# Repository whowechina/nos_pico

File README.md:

# Nos Pico - Nostalgia Style Mini Controller
[点这里可以切换到中文版](README_CN.md)

Currently there're two sizes of Nos Pico. Nos Pico is the small one, suitable for 15 to 17 inch monitors. Nos Pico+ is the larger one, suitable for 24 to 27 inch monitors. There're no differences except the size.

Features:
* All 3D printed parts.
* Velocity sensitive.
* RGB key lights.
* Works as MIDI keyboard.
* HID lights.
* 4 extra programmable buttons.

Thanks to many respectful guys/companies who made their tools or materials free or open source (KiCad, OnShape, InkScape, Raspberry things).

Special thanks to community projects and developers.
And also these projects:
* RP_Silicon_KiCad: https://github.com/HeadBoffin/RP_Silicon_KiCad
* Type-C: https://github.com/ai03-2725/Type-C.pretty

## My Other Projects
You can check out my other cool projects.

* Popn Pico: https://github.com/whowechina/popn_pico
* IIDX Pico: https://github.com/whowechina/iidx_pico
* Chu Pico: https://github.com/whowechina/chu_pico
* Mai Pico: https://github.com/whowechina/mai_pico
* Diva Pico: https://github.com/whowechina/diva_pico
* AIC Pico: https://github.com/whowechina/aic_pico
* Groove Pico: https://github.com/whowechina/groove_pico
* Geki Pico: https://github.com/whowechina/geki_pico
* Musec Pico: https://github.com/whowechina/musec_pico
* Ju Pico: https://github.com/whowechina/ju_pico
* Bishi Pico: https://github.com/whowechina/bishi_pico
* Nos Pico: https://github.com/whowechina/nos_pico
* Voltex Pico: https://github.com/whowechina/voltex_pico
* Chord Pico: https://github.com/whowechina/chord_pico
* Dance Pico: https://github.com/whowechina/dance_pico
* Arcade Pico: https://github.com/whowechina/arcade_pico

## **Disclaimer** ##
I made this project in my personal time with no financial benefit or sponsorship. I will continue to improve the project. I have done my best to ensure that everything is accurate and functional, there's always a chance that mistakes may occur. I cannot be held responsible for any loss of your time or money that may result from using this open source project. Thank you for your understanding.

## About the License
It's CC-NC. So DIY for yourself and for your friend, don't make money from it. And plagiarism that doesn’t even dare to mention the original author is not acceptable. Please note that pooling orders and group buying for raw materials is acceptable.Selling any leftover components at cost (without profit) is also acceptable.

If you're interested in buying from me, or for commercial use, please contact me (Discord, QQ group, Goofish).
* My Discord Invitation: https://discord.gg/M8f2PPQFEA
* QQ Group: 854535476
* Goofish: whowe12345

## HOW TO BUILD
### PCB and Components
* Go JLCPCB or any PCB vendor you like, make order with the gerber zip files (latest `Production\PCB\nos_pico_xxx.zip` for Nos Pico, or `Production\PCB\nos_plus_xxx.zip` for Nos Pico+), regular FR-4 board, black color, **1.6mm** thickness.

* 1x Rasberry Pico Pi Pico or pin-to-pin compatible clones, those with type-C port are strongly recommended.  
  https://www.raspberrypi.com/products/raspberry-pi-pico
* 1x USB Type-C socket (918-418K2023S40001 or KH-TYPE-C-16P)

* 1x ADG732BSUZ (TQFP48) analog multiplexer.  
  https://www.analog.com/en/products/adg732.html
* 1x MBR120VLSFT1G Schottky diode (SOD-123), or any SOD-123 **Schottky** diode with 1A or more current rating.
* 20x to 30x 0603 0.1uF (0.1~1uF all fine) capacitors.
* 3x 0603 5.1kohm resistors, 2 for USB and 1 for signal divider.
* 1x 0603 2kohm resistor for signal divider.
* 28x SS49E linear Hall effect sensors (SOT23).
* 1x Small 3V to 5V DC-DC step up or up-down converter. Make sure its output is 5V and input range covers 3.3V. If the one you get has different pinout, you need to hand wire it. If you don't see the footprint in the PCB, that means it's removed from newer revisions.  
  https://www.dfrobot.com/product-1766.html

* for Nos Pico only:
  * 56x WS2812B-4020 RGB LEDs (side facing)
  * 6x WS2812B-3528 RGB LEDs.
  * 4x HDK KSMC614A or Alps SKRGASD010 switches (6mm\*6mm\*9.5mm).  
    https://www.hdk.co.jp/pdf/spj/spj_ksmc614a.pdf  
    https://www.mouser.com/datasheet/2/15/alps_s_a0002902192_1-2258679.pdf
    
* for Nos Pico+ only:
  * 62x WS2812B-3528 RGB LEDs.
  * 4x Kailh Box Cream Pro switches.  
    https://www.kailh.net/products/kailh-box-cream-pro-switch-set

* Note: in newer revisions, the DC/DC is removed, use the following components instead.
  * 1x TPS7A2042PDBVR (4.2V) or LP5907MFX-4.5 (4.5V) LDO (SOT23-5), (U7).  
    https://www.ti.com/product/TPS7A20/part-details/TPS7A2042PDBVR
  * 1x LM4040 3.0V Shunt Voltage Reference, in SOT23-3 (U6). There're many models; make sure it's 3.0V and in an SOT23-3 package.
  * R1 and R2 are 2Kohm and 5.1Kohm 0603 resistors, respectively.

* This is how Nos Pico looks after soldering.  

* This is how Nos Pico+ looks after soldering.  

### Notes
1. About the 2 USB holes, you decide whether to solder them or not.   

   * If you solder these 2 hole pins.
     * Pros: ether USB ports can be used for host communication; if your pico has a micro USB port, now you'll have a Type-C port and a micro USB port.
     * Cons: if one port is for host communication, the other port can use for power supply, but only from power bank or charger, not from a USB data port.

   * Or you don't solder them (and also better use thin tape to cover the pins on Pi Pico).
     * Pros: only the port from Pi Pico can be used for host communication, the other port can only be used for power supply.
     * Cons: the power supply port can connect to any USB port, inluding USB data ports, power banks or chargers.

2. There're so many capacitors for de-coupling. You don't need to solder them all. You can solder some of them, just distribute them evenly. The one near the multiplexer is a must.

3. Leave C30 un-soldered.

### Test the PCB
* You can test the PCB now, put the firmware in.
* Very likely all key LEDs will light up in white.
* Logo LEDs will slowly change color.
* Nos Pico should be recognized as a USB HID device, here's the test page.  
  https://greggman.github.io/html5-gamepad-test/
* The test page responds to the 4 button switches.
* Use the terminal tool to connect to Nos Pico's command line interface.
  https://googlechromelabs.github.io/serial-terminal/
* Keep the PCB away from magnetic field, such as speakers or motors and execute `calibrate origin`. All values should be similar and near 2200.
* If you notice strange values, you need to check the soldering of the muxiplexer and corresponding hall effect sensor.

### 3D Printing
#### Printing parameters  
* PLA or PETG.
* Layer height: 0.2mm
* Wall: 2 to 3.
* Support: No, unless explicitly mentioned.
* Files are always in milimeter unit, not inch.

#### Parts
* All files are in `Production\3DPrint` folder.
* File names started with `Nos Pico -` are for Nos Pico, and `Nos Pico+ -` are for Nos Pico+.

* Keys: `Key.3mf`. Print 28 keys, 8 all-white, and 20 white-with-black tops (with "black key"). You need multi-color printing for the keys, or you need to manually paint the black part.  
  
* Base: `Base_*.stl`, all in light apricot color.
* Rear: `Rear_*.stl`, all in light apricot color. Make the side with the screws as the bottom and **enable support**.
* Support: `Support_*.stl`, Left and Right are in light apricot color and Center is in white color.
* Panel: `Panel_*.stl`, Left and Right are in light apricot color. The Center is in white color with the black logo on top. You can use multi-color to print it or paint it manually.

### Assembly
#### Other components needed
Please note that the quantities of the screws are approximate.

* 10x M3\*6mm screws for the PCB to the base parts.
* 20x M3\*8mm screws for support parts to the base parts.
* 16x M3\*8mm screws for rear parts to the base parts.
* 20x M2\*8mm countersunk screws for the panels to the support parts.
* Some 2.5mm~3mm thick self-adhesive foam tape (Poron or EVA).
* Some 1mm~1.5mm thick self-adhesive foam tape (Poron or EVA).

* 28x 0.4\*5\*10\*6N (0.4mm wire diameter, 5mm outer diameter, 10mm free length, 6 turns) springs.
* Some white silicone adhesive, such as K-704 silicone industrial adhesive.

* Some 10mm diameter silicone self-adhesive anti-slip pads.  

* For Nos Pico only.
  * 1x 2mm\*361mm stainless steel wire shaft.
  * 28x 2mm\*2mm axial magnetized cylinder magnets (2mm diameter, 2mm height).

* For Nos Pico+ only.
  * 1x 2mm\*573mm stainless steel wire shaft.
  * 28x 3mm\*2mm axial magnetized cylinder magnets (3mm diameter, 2mm height).

#### Steps
Please note that the pictures in this section are mixed with Nos Pico and Nos Pico+, some are even from prototype. But the assembly steps are the same. So ignore the differences in some details.

1. Use the M3\*6mm screws to fix the PCB to the base part.  
   
2. Apply the 2.5mm thick foam tape on PCB, right below the hall effect sensors. It damps the key press noise. 3mm width is recommended for Nos Pico, and 5mm width is recommended for Nos Pico+.  
   
3. Use the M3*8mm screws to fix the support parts to the base part.  
   
4. Insert the steel shafts into keys and install them into the base parts. Please note the key arrangements.  

5. Rotate the keys to the other side to insert the magnets into the keys. Cylinder magnets should be placed vertically. You need some glue or silicone adhesive to fix them in place.

6. Install the springs on the base parts, and rotate the keys onto them.

7. Now we temporarily calibrate and test the keys use `calibrate travel` command. Leave the keys un-pressed before executing the command, 1 second later, gently press down all the keys (not neccessarily all of them simultanously, just to cover them all). After calibration, keys are ready for play. You can use some MIDI software to test the keys. If all keys work fine, you can proceed to the next step. If not, you need to check the soldering of the hall effect sensors and the multiplexer.  
   
8. Apply the 1mm thick foam tape on the edge of the panel parts. It damps the key release noise.  
   
9.  Use the M2*8mm countersunk screws to fix the panel parts to the support parts.  
    
10. Use the M3*10mm screws to fix the rear parts to the base parts. Please note that left and right rear parts have a shaft limit slot, which is blocked by thin walls working as print support, you need to cut them open.  
    
11. Now calibrate the key travel again use `calibrate travel` command, don't forget to gently press down all the keys 1 second after executing the command.
12. Apply the silicone self-adhesive anti-slip pads on the bottom of the base parts.  
    
13. Congratulations, you finished!

#### Caution
* Don't use `calibrate origin` command after the assembly. It can only be used when there's no magnets installed.
* Screws are easy to break 3D printed parts. So don't screw them too fast or too tight. When you notice the resistance suddenly increases, stop immediately.

### Firmware
* UF2 file is in `Production\Firmware` folder.
* For the new build, hold the BOOTSEL button while connect the USB to a PC, there will be a disk named "RPI-RP2" showed up. Drag the UF2 firmware binary file into it. That's it. Note that there's a small hole on the bottom side of the Nos Pico, aligned with the BOOTSEL button.
* If it's already running Nos Pico firmware, you can either use "update" in command line or hold down left 2 buttons while connecting to USB to enter update mode.
* To access the command line, you can use this Web Serial Terminal to connect to the command line port of the controller. (Note: "?" is for help)  
  https://googlechromelabs.github.io/serial-terminal/

### Usage
* By default, it works as a MIDI keyboard. Just plug and play.
* You can change the report to HID buttons, or HID analog values (axis) with `hid *` command.
* You can change the key light mode using `light *` command.
* You can change the light brightness using `level <key|logo>` command.
* You can do live setting without the command line interface. Let's call the 4 auxilary keys are L1, L2, R1, R2. Pressing all of them at the same time will enter the live setting mode.
  * L1 and L2 are for navigating the setting items. The logo light shows current item. The items are:
    * Brightness for Piano Key Light
    * Brightness for Logo Light
    * Piano Key Light Mode (Off, Switch, Pressure, Velocity)
  * R1 is Cancel, R2 is Confirm.
  * The piano keys are for changing the values of the setting items.  

## CAD Source File
I'm using OnShape free subscription. It's powerful but it can't archive original designs to local, so I can only share the link here. STL/DXF/DWG files are exported from this online document.  
  https://cad.onshape.com/documents/0429d4b0d9d82f8289fdce7e/w/647e985c461e79dd4ff63d99/e/9dea2fe40b32c7a64632a585

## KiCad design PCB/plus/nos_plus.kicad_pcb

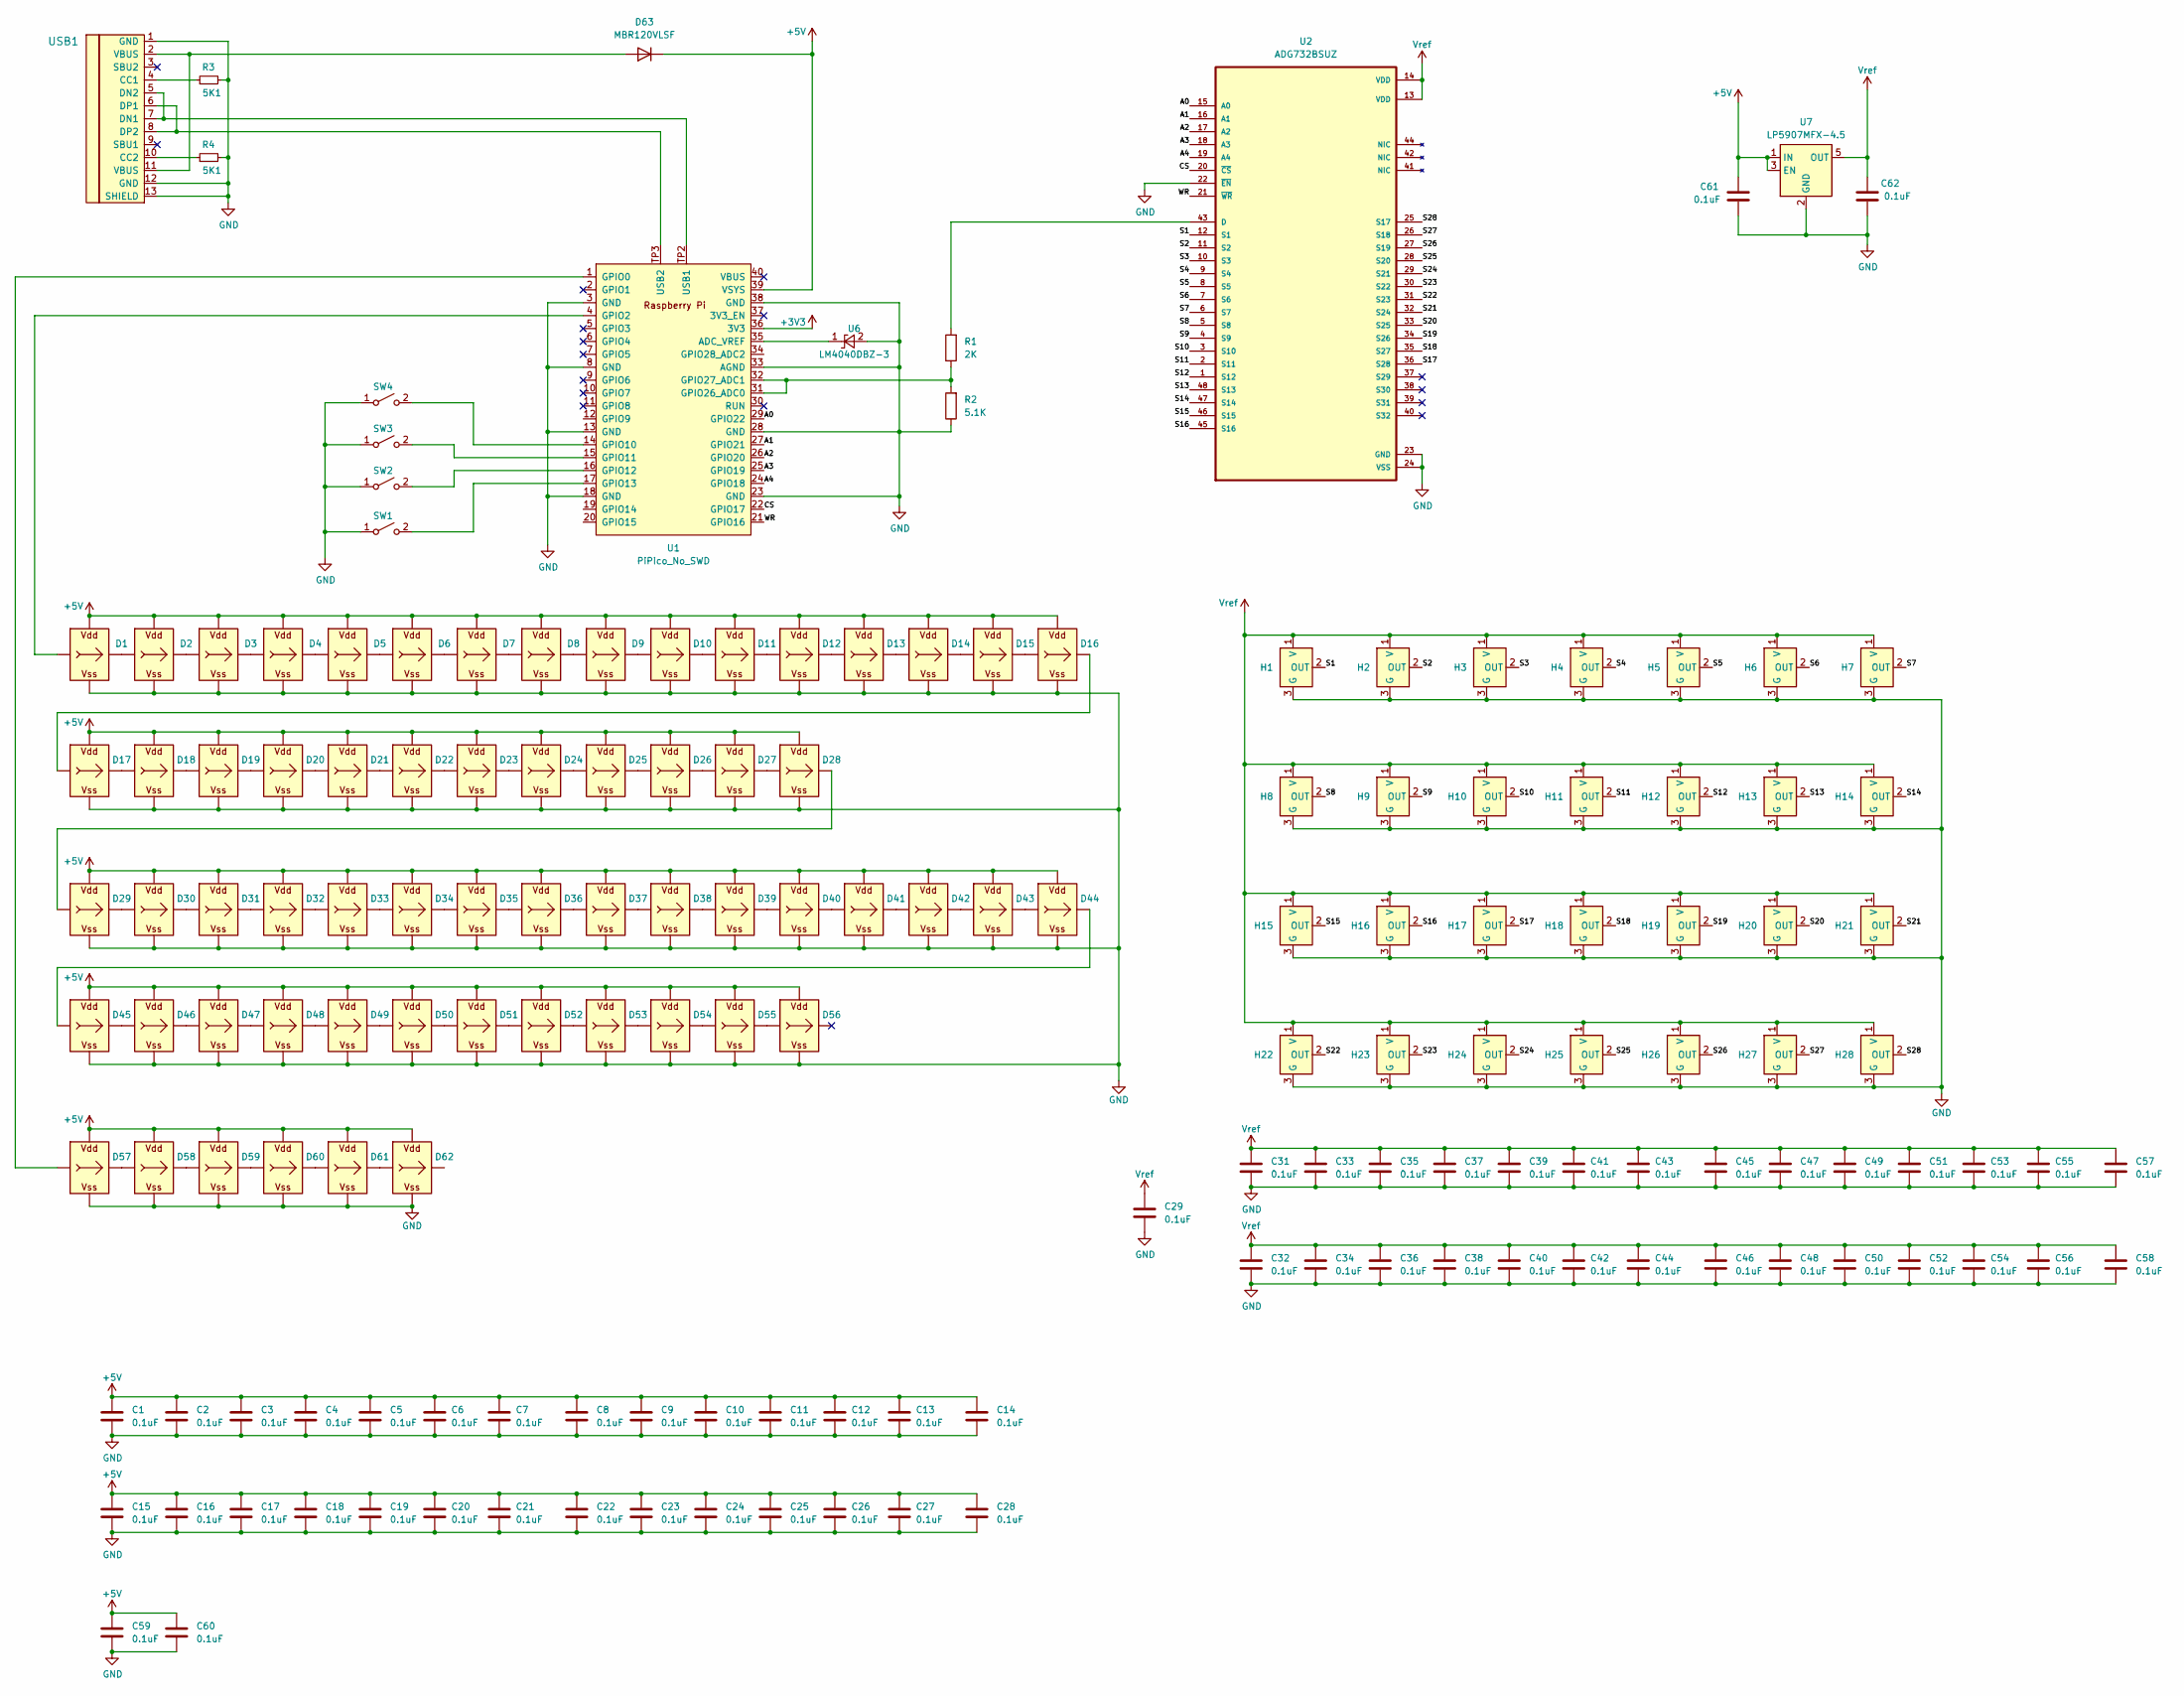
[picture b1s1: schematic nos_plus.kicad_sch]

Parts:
C1, C2, C3, C4, C5, C6, C7, C8, C9, C10, C11, C12, C13, C14, C15, C16, C17, C18, C19, C20, C21, C22, C23, C24, C25, C26, C27, C28, C29, C31, C32, C33, C34, C35, C36, C37, C38, C39, C40, C41, C42, C43, C44, C45, C46, C47, C48, C49, C50, C51, C52, C53, C54, C55, C56, C57, C58, C59, C60, C61, C62: 0.1uF; C_0603_1608Metric_Pad1.08x0.95mm_HandSolder
D1, D2, D3, D4, D5, D6, D7, D8, D9, D10, D11, D12, D13, D14, D15, D16, D17, D18, D19, D20, D21, D22, D23, D24, D25, D26, D27, D28, D29, D30, D31, D32, D33, D34, D35, D36, D37, D38, D39, D40, D41, D42, D43, D44, D45, D46, D47, D48, D49, D50, D51, D52, D53, D54, D55, D56, D57, D58, D59, D60, D61, D62: WS2812B_Unified; WS2812B-2835
D63: MBR120VLSF; D_SOD-123_LONG
H1, H2, H3, H4, H5, H6, H7, H8, H9, H10, H11, H12, H13, H14, H15, H16, H17, H18, H19, H20, H21, H22, H23, H24, H25, H26, H27, H28: SS49E_SOT23; SOT-23-FAT
R1: 2K; R_0603_1608Metric_Pad0.98x0.95mm_HandSolder
R2: 5.1K; R_0603_1608Metric_Pad0.98x0.95mm_HandSolder
R3, R4: 5K1; R_0603_1608Metric_Pad0.98x0.95mm_HandSolder; LCSC C23186
SW1, SW2, SW3, SW4: SW_SPST; SW_Choc_V1V2_Cherry_MX_LED
U1: PiPico_No_SWD; RPi_Pico_SMD_Pins_No_SWD
U2: ADG732BSUZ; QFP50P900X900X120-49N
U6: LM4040DBZ-3; SOT-23-FAT
U7: LP5907MFX-4.5; SOT-23-5
USB1: U262-161N-4BVC11; HRO-TYPE-C-31-M-12-Assembly; LCSC C319148

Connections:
+3V3: U1.36 (3V3)
+5V: C1.1, C2.1, C3.1, C4.1, C5.1, C6.1, C7.1, C8.1, C9.1, C10.1, C11.1, C12.1, C13.1, C14.1, C15.1, C16.1, C17.1, C18.1, C19.1, C20.1, C21.1, C22.1, C23.1, C24.1, C25.1, C26.1, C27.1, C28.1, C59.1, C60.1, C61.1, D1.V (VDD), D2.V (VDD), D3.V (VDD), D4.V (VDD), D5.V (VDD), D6.V (VDD), D7.V (VDD), D8.V (VDD), D9.V (VDD), D10.V (VDD), D11.V (VDD), D12.V (VDD), D13.V (VDD), D14.V (VDD), D15.V (VDD), D16.V (VDD), D17.V (VDD), D18.V (VDD), D19.V (VDD), D20.V (VDD), D21.V (VDD), D22.V (VDD), D23.V (VDD), D24.V (VDD), D25.V (VDD), D26.V (VDD), D27.V (VDD), D28.V (VDD), D29.V (VDD), D30.V (VDD), D31.V (VDD), D32.V (VDD), D33.V (VDD), D34.V (VDD), D35.V (VDD), D36.V (VDD), D37.V (VDD), D38.V (VDD), D39.V (VDD), D40.V (VDD), D41.V (VDD), D42.V (VDD), D43.V (VDD), D44.V (VDD), D45.V (VDD), D46.V (VDD), D47.V (VDD), D48.V (VDD), D49.V (VDD), D50.V (VDD), D51.V (VDD), D52.V (VDD), D53.V (VDD), D54.V (VDD), D55.V (VDD), D56.V (VDD), D57.V (VDD), D58.V (VDD), D59.V (VDD), D60.V (VDD), D61.V (VDD), D62.V (VDD), D63.1 (K), U1.39 (VSYS), U7.1 (IN), U7.3 (EN)
/A0: U1.29 (GPIO22), U2.15 (A0)
/A1: U1.27 (GPIO21), U2.16 (A1)
/A2: U1.26 (GPIO20), U2.17 (A2)
/A3: U1.25 (GPIO19), U2.18 (A3)
/A4: U1.24 (GPIO18), U2.19 (A4)
/CS: U1.22 (GPIO17), U2.20 (~CS)
/S1: H1.2 (OUT), U2.12 (S1)
/S2: H2.2 (OUT), U2.11 (S2)
/S3: H3.2 (OUT), U2.10 (S3)
/S4: H4.2 (OUT), U2.9 (S4)
/S5: H5.2 (OUT), U2.8 (S5)
/S6: H6.2 (OUT), U2.7 (S6)
/S7: H7.2 (OUT), U2.6 (S7)
/S8: H8.2 (OUT), U2.5 (S8)
/S9: H9.2 (OUT), U2.4 (S9)
/S10: H10.2 (OUT), U2.3 (S10)
/S11: H11.2 (OUT), U2.2 (S11)
/S12: H12.2 (OUT), U2.1 (S12)
/S13: H13.2 (OUT), U2.48 (S13)
/S14: H14.2 (OUT), U2.47 (S14)
/S15: H15.2 (OUT), U2.46 (S15)
/S16: H16.2 (OUT), U2.45 (S16)
/S17: H17.2 (OUT), U2.36 (S28)
/S18: H18.2 (OUT), U2.35 (S27)
/S19: H19.2 (OUT), U2.34 (S26)
/S20: H20.2 (OUT), U2.33 (S25)
/S21: H21.2 (OUT), U2.32 (S24)
/S22: H22.2 (OUT), U2.31 (S23)
/S23: H23.2 (OUT), U2.30 (S22)
/S24: H24.2 (OUT), U2.29 (S21)
/S25: H25.2 (OUT), U2.28 (S20)
/S26: H26.2 (OUT), U2.27 (S19)
/S27: H27.2 (OUT), U2.26 (S18)
/S28: H28.2 (OUT), U2.25 (S17)
/WR: U1.21 (GPIO16), U2.21 (~WR)
GND: C1.2, C2.2, C3.2, C4.2, C5.2, C6.2, C7.2, C8.2, C9.2, C10.2, C11.2, C12.2, C13.2, C14.2, C15.2, C16.2, C17.2, C18.2, C19.2, C20.2, C21.2, C22.2, C23.2, C24.2, C25.2, C26.2, C27.2, C28.2, C29.2, C31.2, C32.2, C33.2, C34.2, C35.2, C36.2, C37.2, C38.2, C39.2, C40.2, C41.2, C42.2, C43.2, C44.2, C45.2, C46.2, C47.2, C48.2, C49.2, C50.2, C51.2, C52.2, C53.2, C54.2, C55.2, C56.2, C57.2, C58.2, C59.2, C60.2, C61.2, C62.2, D1.G (VSS), D2.G (VSS), D3.G (VSS), D4.G (VSS), D5.G (VSS), D6.G (VSS), D7.G (VSS), D8.G (VSS), D9.G (VSS), D10.G (VSS), D11.G (VSS), D12.G (VSS), D13.G (VSS), D14.G (VSS), D15.G (VSS), D16.G (VSS), D17.G (VSS), D18.G (VSS), D19.G (VSS), D20.G (VSS), D21.G (VSS), D22.G (VSS), D23.G (VSS), D24.G (VSS), D25.G (VSS), D26.G (VSS), D27.G (VSS), D28.G (VSS), D29.G (VSS), D30.G (VSS), D31.G (VSS), D32.G (VSS), D33.G (VSS), D34.G (VSS), D35.G (VSS), D36.G (VSS), D37.G (VSS), D38.G (VSS), D39.G (VSS), D40.G (VSS), D41.G (VSS), D42.G (VSS), D43.G (VSS), D44.G (VSS), D45.G (VSS), D46.G (VSS), D47.G (VSS), D48.G (VSS), D49.G (VSS), D50.G (VSS), D51.G (VSS), D52.G (VSS), D53.G (VSS), D54.G (VSS), D55.G (VSS), D56.G (VSS), D57.G (VSS), D58.G (VSS), D59.G (VSS), D60.G (VSS), D61.G (VSS), D62.G (VSS), H1.3 (G), H2.3 (G), H3.3 (G), H4.3 (G), H5.3 (G), H6.3 (G), H7.3 (G), H8.3 (G), H9.3 (G), H10.3 (G), H11.3 (G), H12.3 (G), H13.3 (G), H14.3 (G), H15.3 (G), H16.3 (G), H17.3 (G), H18.3 (G), H19.3 (G), H20.3 (G), H21.3 (G), H22.3 (G), H23.3 (G), H24.3 (G), H25.3 (G), H26.3 (G), H27.3 (G), H28.3 (G), R2.1, R3.2, R4.2, SW1.1 (A), SW2.1 (A), SW3.1 (A), SW4.1 (A), U1.3 (GND), U1.8 (GND), U1.13 (GND), U1.18 (GND), U1.23 (GND), U1.28 (GND), U1.33 (AGND), U1.38 (GND), U2.22 (~EN), U2.23 (GND), U2.24 (VSS), U6.2 (A), U7.2 (GND), USB1.1 (GND), USB1.12 (GND), USB1.13 (SHIELD)
unnamed: D1.I (In), U1.4 (GPIO2)
unnamed: D1.O (Out), D2.I (In)
unnamed: D2.O (Out), D3.I (In)
unnamed: D3.O (Out), D4.I (In)
unnamed: D4.O (Out), D5.I (In)
unnamed: D5.O (Out), D6.I (In)
unnamed: D6.O (Out), D7.I (In)
unnamed: D7.O (Out), D8.I (In)
unnamed: D8.O (Out), D9.I (In)
unnamed: D9.O (Out), D10.I (In)
unnamed: D10.O (Out), D11.I (In)
unnamed: D11.O (Out), D12.I (In)
unnamed: D12.O (Out), D13.I (In)
unnamed: D13.O (Out), D14.I (In)
unnamed: D14.O (Out), D15.I (In)
unnamed: D15.O (Out), D16.I (In)
unnamed: D16.O (Out), D17.I (In)
unnamed: D17.O (Out), D18.I (In)
unnamed: D18.O (Out), D19.I (In)
unnamed: D19.O (Out), D20.I (In)
unnamed: D20.O (Out), D21.I (In)
unnamed: D21.O (Out), D22.I (In)
unnamed: D22.O (Out), D23.I (In)
unnamed: D23.O (Out), D24.I (In)
unnamed: D24.O (Out), D25.I (In)
unnamed: D25.O (Out), D26.I (In)
unnamed: D26.O (Out), D27.I (In)
unnamed: D27.O (Out), D28.I (In)
unnamed: D28.O (Out), D29.I (In)
unnamed: D29.O (Out), D30.I (In)
unnamed: D30.O (Out), D31.I (In)
unnamed: D31.O (Out), D32.I (In)
unnamed: D32.O (Out), D33.I (In)
unnamed: D33.O (Out), D34.I (In)
unnamed: D34.O (Out), D35.I (In)
unnamed: D35.O (Out), D36.I (In)
unnamed: D36.O (Out), D37.I (In)
unnamed: D37.O (Out), D38.I (In)
unnamed: D38.O (Out), D39.I (In)
unnamed: D39.O (Out), D40.I (In)
unnamed: D40.O (Out), D41.I (In)
unnamed: D41.O (Out), D42.I (In)
unnamed: D42.O (Out), D43.I (In)
unnamed: D43.O (Out), D44.I (In)
unnamed: D44.O (Out), D45.I (In)
unnamed: D45.O (Out), D46.I (In)
unnamed: D46.O (Out), D47.I (In)
unnamed: D47.O (Out), D48.I (In)
unnamed: D48.O (Out), D49.I (In)
unnamed: D49.O (Out), D50.I (In)
unnamed: D50.O (Out), D51.I (In)
unnamed: D51.O (Out), D52.I (In)
unnamed: D52.O (Out), D53.I (In)
unnamed: D53.O (Out), D54.I (In)
unnamed: D54.O (Out), D55.I (In)
unnamed: D55.O (Out), D56.I (In)
unnamed: D57.I (In), U1.1 (GPIO0)
unnamed: D57.O (Out), D58.I (In)
unnamed: D58.O (Out), D59.I (In)
unnamed: D59.O (Out), D60.I (In)
unnamed: D60.O (Out), D61.I (In)
unnamed: D61.O (Out), D62.I (In)
unnamed: D63.2 (A), USB1.2 (VBUS), USB1.11 (VBUS)
unnamed: SW1.2 (B), U1.17 (GPIO13)
unnamed: SW2.2 (B), U1.16 (GPIO12)
unnamed: SW3.2 (B), U1.15 (GPIO11)
unnamed: SW4.2 (B), U1.14 (GPIO10)
unnamed: U1.35 (ADC_VREF), U6.1 (K)
unnamed: R1.1, R2.2, U1.31 (GPIO26_ADC0), U1.32 (GPIO27_ADC1)
unnamed: U1.TP2 (USB1), USB1.5 (DN2), USB1.7 (DN1)
unnamed: U1.TP3 (USB2), USB1.6 (DP1), USB1.8 (DP2)
unnamed: R1.2, U2.43 (D)
unnamed: R3.1, USB1.4 (CC1)
unnamed: R4.1, USB1.10 (CC2)
Vref: C29.1, C31.1, C32.1, C33.1, C34.1, C35.1, C36.1, C37.1, C38.1, C39.1, C40.1, C41.1, C42.1, C43.1, C44.1, C45.1, C46.1, C47.1, C48.1, C49.1, C50.1, C51.1, C52.1, C53.1, C54.1, C55.1, C56.1, C57.1, C58.1, C62.1, H1.1 (V), H2.1 (V), H3.1 (V), H4.1 (V), H5.1 (V), H6.1 (V), H7.1 (V), H8.1 (V), H9.1 (V), H10.1 (V), H11.1 (V), H12.1 (V), H13.1 (V), H14.1 (V), H15.1 (V), H16.1 (V), H17.1 (V), H18.1 (V), H19.1 (V), H20.1 (V), H21.1 (V), H22.1 (V), H23.1 (V), H24.1 (V), H25.1 (V), H26.1 (V), H27.1 (V), H28.1 (V), U2.13 (VDD), U2.14 (VDD), U7.5 (OUT)

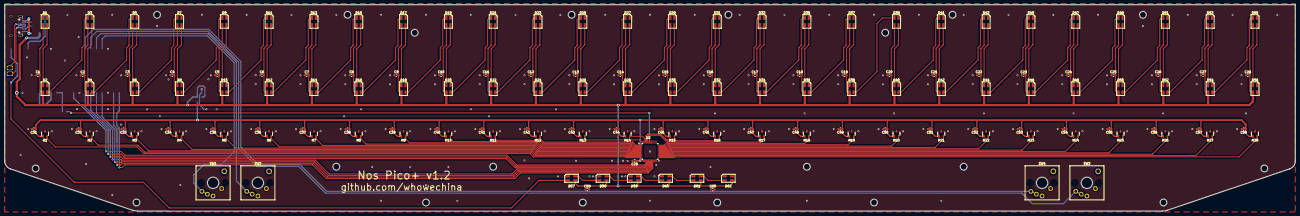
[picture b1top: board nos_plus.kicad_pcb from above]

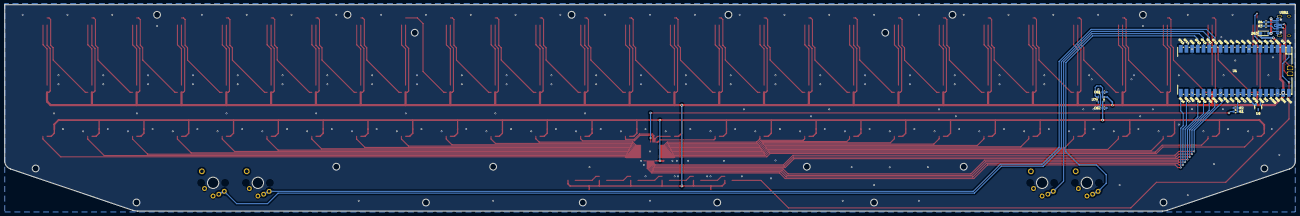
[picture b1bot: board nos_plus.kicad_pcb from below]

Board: 2 copper layers, 576.0 x 92.1 mm, 165 parts (11 on the bottom side), 112 nets.

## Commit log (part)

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2025-02-28 Initial upload
2025-02-28 PCB work just started
2025-02-28 Change PCB folder
2025-02-28 PCB progress 60%
2025-03-01 PCB progress 80%
2025-03-01 PCB v1.0 done
2025-03-09 Basic working firmware
2025-03-11 MIDI support
2025-03-12 PCB v1.1 for dual USB port
2025-03-13 PCB v1.11 fix housing interference
2025-03-14 Better velocity calculation
2025-03-15 Calibrate hall sensor rigin and debug
2025-03-15 Slower light change
2025-03-15 Fix velocity sensitive light
2025-03-16 HID setting commands
2025-03-16 Light mode selection
2025-03-19 Nos Pico Plus begins
2025-03-20 Nos Pico PCB v1.12 (isolate vbus)
2025-03-21 Nos Pico+ PCB v1.0
2025-03-24 Button support and faster clock/fps
2025-03-24 Better velocity with the help of faster fps
2025-03-24 Button in HID report
2025-03-28 PCB project update
2025-03-28 Upload 3D Print files
2025-03-28 Faster sample rate
2025-03-28 Remain at 4k sample rate for consistency
2025-03-29 Lower default light brightness
2025-03-30 Guide in English
2025-03-31 Finish English guide
2025-03-31 A note in guide (for mixed pictures)
2025-04-02 HID light support
2025-04-02 Nos Pico + PCB v1.01 (footprint finetune)
2025-04-03 Nos Pico PCB v1.2 (add buttons)
2025-04-03 Guide in Chinese
2025-04-03 Better button holes for Nos Pico
2025-04-04 Minor change may help the power ripple
2025-04-08 Live setup for light level and mode
2025-04-14 Adjust hall effect sensor model #
    Just a small change since the family is right but the model number for the SOT23 package is wrong.
2025-10-12 Update stainless steel wire option
2025-10-13 Readme for live setup
2025-10-16 Sensor runtime debug
2025-10-16 PCB v1.2, remove unnecessary components
2026-03-09 Shaft-end wobble elimination
2026-03-09 Keep reference up to date
2026-03-11 Doc reference update
